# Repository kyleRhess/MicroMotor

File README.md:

# MicroMotor

## A three-phase BLDC motor driver with a rotary encoder interface and serial communication via USB.
## [More project details can be found here.](https://kylerhess.github.io/umotor.html)
\
 This code has been written for and tested on an ARM STM32F410 processor.
\
\
The rotary encoder interface was originally developed in my [EncoderQ](https://github.com/kyleRhess/EncoderQ) project.
\
\
The only rotary encoder that has been tested so far is the [Omron E6D-C](http://www.ia.omron.com/data_pdf/cat/e6d-c_ds_e_5_1_csm497.pdf).
\
\
The only BLDC motor that has been tested so far is the [Maxon EC 339268](https://www.maxongroup.com/medias/sys_master/root/8841185394718/EN-282.pdf). The motor requirement is that it must include Hall sensor output for position sensing. Back-EMF control is not currently supported.

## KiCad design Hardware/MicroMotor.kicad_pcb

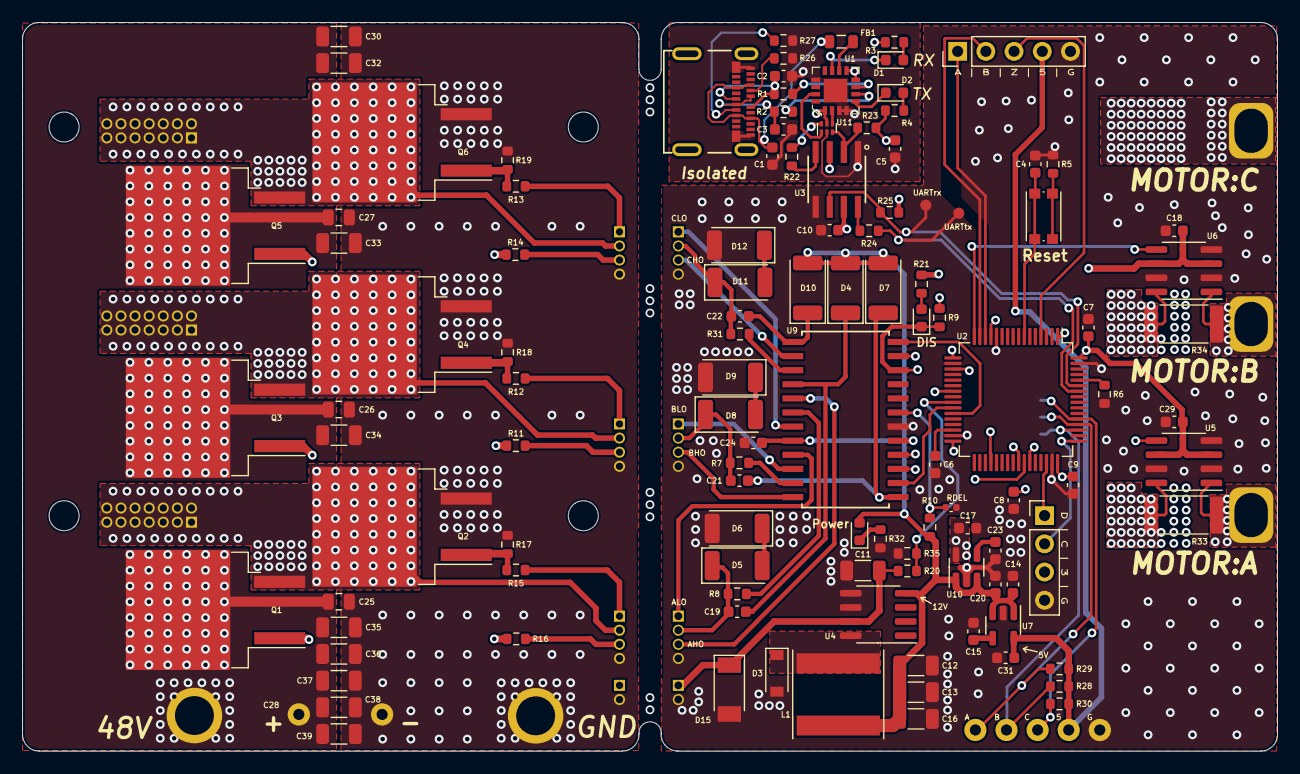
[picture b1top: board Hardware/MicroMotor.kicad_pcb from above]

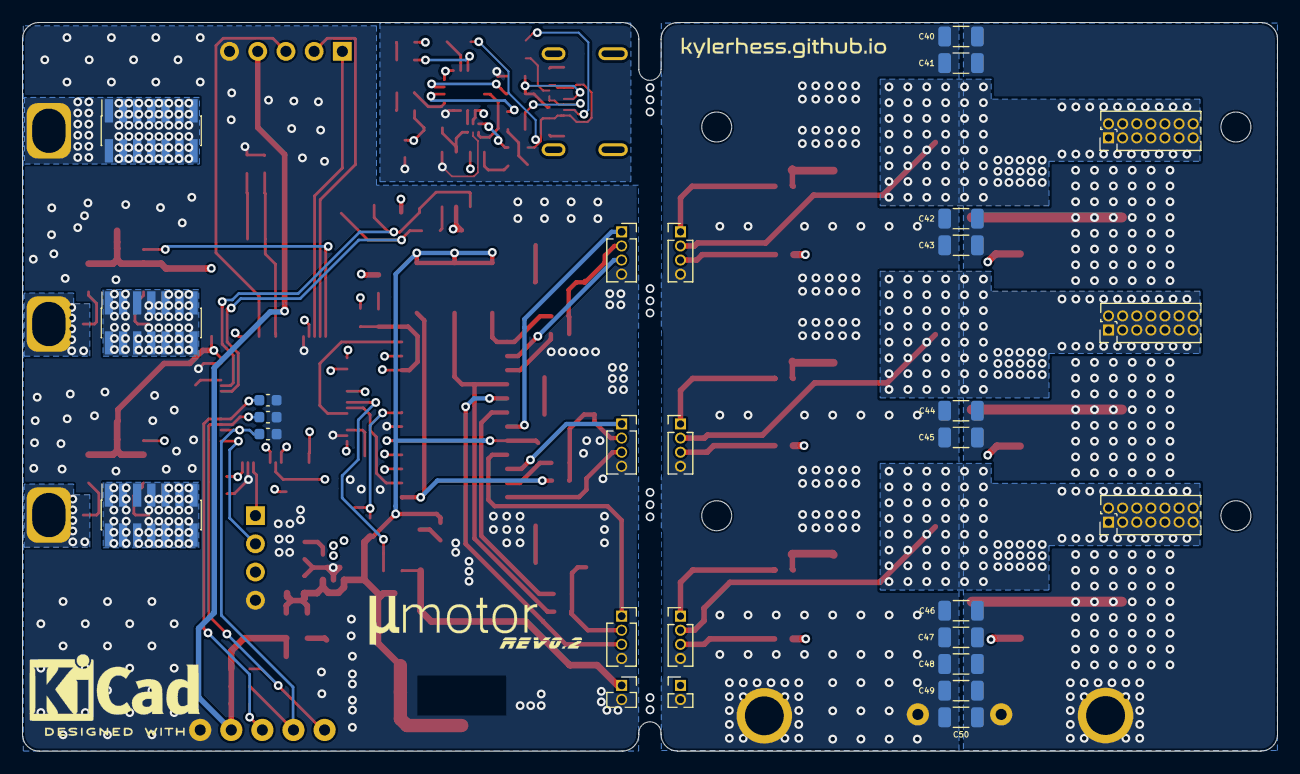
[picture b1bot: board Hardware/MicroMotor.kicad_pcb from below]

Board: 4 copper layers, 113.0 x 65.6 mm, 149 parts (28 on the bottom side), 81 nets.

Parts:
5: TestPoint_Loop_D2.50mm_Drill1.0mm
48V: TestPoint_THTPad_D4.0mm_Drill2.0mm
A: TestPoint_Plated_Hole_D3.0mm
A#2: TestPoint_Loop_D2.50mm_Drill1.0mm
B: TestPoint_Plated_Hole_D3.0mm
B#2: TestPoint_Loop_D2.50mm_Drill1.0mm
C: TestPoint_Plated_Hole_D3.0mm
C1, C9, C15, C23: 10nF; C_0603_1608Metric
C2, C3: 47pF; C_0603_1608Metric
C4, C5, C8, C10, C18, C29: 0.1uF; C_0603_1608Metric
C6, C7: 2.2uF; C_0603_1608Metric
C11: 1uF; C_1206_3216Metric
C12, C13, C16: 47uF; C_1206_3216Metric
C14, C17, C20, C24, C31: 1uF; C_0603_1608Metric
C19, C21, C22: 0.22uF; C_0603_1608Metric
C25, C26, C27: 1uF; C_0805_2012Metric
C28: 1000uF; C_Radial_D18.0mm_H35.5mm_P7.50mm
C30, C32, C33, C34, C35, C36, C37, C38, C39, C40, C41, C42, C43, C44, C45, C46, C47, C48, C49, C50: 4.7uF; C_1206_3216Metric
C#2: TestPoint_Loop_D2.50mm_Drill1.0mm
D1, D2, D13, D14: LED; LED_0603_1608Metric
D3: 60V 500mA; D_SOD-123
D4, D5, D6, D7, D8, D9, D10, D11, D12: D; D_2010_5025Metric
D15: SMA6S56A; D_SOD-128
FB1: 1.5A; L_0805_2012Metric
G: TestPoint_Loop_D2.50mm_Drill1.0mm
GND: TestPoint_THTPad_D4.0mm_Drill2.0mm
J1: USB_C_Receptacle_USB2.0; USB_C_1054500101
J2: Conn_01x04_Male; PinHeader_1x04_P2.54mm_Vertical
J3: Conn_01x05_Male; PinHeader_1x05_P2.54mm_Vertical
J4, J5, J6: Conn_01x04_Male; PinHeader_1x04_P1.27mm_Vertical
J7, J8, J9: Conn_02x06_Odd_Even; PinHeader_2x07_P1.27mm_Vertical
J10, J11, J12: Conn_02x06_Odd_Even; PinSocket_2x07_P1.27mm_Vertical_SMD
J13, J14, J15: Conn_01x04_Female; PinSocket_1x04_P1.27mm_Vertical
J16: Conn_01x02_Male; PinHeader_1x02_P1.27mm_Vertical
J17: Conn_01x02_Female; PinSocket_1x02_P1.27mm_Vertical
L1: 100uH; L_Taiyo-Yuden_NR-80xx
Q1, Q2, Q3, Q4, Q5, Q6: FDB075N15A; TO-263-2
R1, R2: 27; R_0603_1608Metric
R3, R4, R21, R22, R24: 330; R_0603_1608Metric
R5: 470; R_0603_1608Metric
R6, R20, R28, R29, R30, R32: 10k; R_0603_1608Metric
R7, R8, R31: 1.2; R_0603_1608Metric
R9, R17, R18, R19: 100k; R_0603_1608Metric
R10: 50k; R_0603_1608Metric
R11, R12, R13, R14, R15, R16: 22; R_0603_1608Metric
R23, R25: 1k; R_0603_1608Metric
R26, R27: 5.1k; R_0603_1608Metric
R33, R34: 750u; R_2512_6332Metric
R35: 576; R_0603_1608Metric
RDEL: C_0402_1005Metric
SW1: SW_Push; SW_Push_1P1T_NO_CK_KMR2
U1: FT230XQ-T; WQFN-16-1EP_4x4mm
U2: STM32F410RBTx; LQFP-64_10x10mm_P0.5mm
U3: ACSL-6210-00RE
U4: LM2594HVM-12; SOIC-8_3.9x4.9mm_P1.27mm
U5, U6: INA240A3D; SOIC-8_3.9x4.9mm_P1.27mm
U7: LP2985-5.0; SOT-23-5
U9: HIP4086ABZ
U10: LP2985-3.3; SOT-23-5
U11: NC7WZ04; Fairchild_MicroPak-6_1.0x1.45mm_P0.5mm
UARTrx: TestPoint_Pad_D1.0mm
UARTtx: TestPoint_Pad_D1.0mm

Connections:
3v3Out: C5.1, R3.1, R4.1, R23.1, U1.1, U1.8, U1.9, U3.3, U11.5
5V_Out: 5.1, C31.2, J3.4, R28.2, R29.2, R30.2, U7.5
12V_Out: C12.2, C13.2, C14.2, C16.2, C20.2, C24.1, D4.2, D7.2, D10.2, D13.2, L1.2, R10.1, U4.4, U7.1, U7.3, U9.20, U10.1, U10.3
+3V3: C7.1, C8.1, C9.1, C10.1, C17.2, C18.2, C29.2, J2.3, R9.1, R21.1, R25.1, U2.1, U2.13, U2.19, U2.32, U2.48, U2.64, U3.7, U5.3, U5.6, U6.3, U6.6, U10.5
+48V: 48V.1, C11.2, C25.1, C26.1, C27.1, C28.1, C30.1, C32.1, C33.1, C34.1, C35.1, C36.1, C37.1, C38.1, C39.1, C40.1, C41.1, C42.1, C43.1, C44.1, C45.1, C46.1, C47.1, C48.1, C49.1, C50.1, D15.1, J16.1, J17.1, Q1.2, Q3.2, Q5.2, R20.2, U4.7
-RXD: U1.2, U11.4
/VBUS: C1.1, FB1.2, J1.A4, J1.A9, J1.B4, J1.B9
AHB: C19.1, D4.1, U9.16
AHI: U2.23, U9.5
AHO: Q1.1, R16.2
AHO_r: J6.3, J15.3, R16.1, U9.17
ALI: U2.41, U9.4
ALO: Q2.1, R15.2, R17.1
ALO_r: J6.1, J15.1, R15.1, U9.21
A_OUT: A.1, R33.1, U5.1
A_SENS: U2.17, U5.5
BHB: C21.1, D7.1, U9.1
BHI: U2.26, U9.2
BHO: Q3.1, R11.2
BHO_r: J5.3, J14.3, R11.1, U9.24
BLI: U2.42, U9.3
BLO: Q4.1, R12.2, R18.1
BLO_r: J5.1, J14.1, R12.1, U9.22
B_OUT: B.1, R34.1, U6.1
B_SENS: U2.16, U6.5
CHB: C22.1, D10.1, U9.13
CHI: U2.27, U9.12
CHO: Q5.1, R14.2
CHO_r: J4.3, J13.3, R14.1, U9.14
CLI: U2.43, U9.11
CLO: Q6.1, R13.2, R19.1
CLO_r: J4.1, J13.1, R13.1, U9.19
DIS: D14.1, R9.2, U2.36, U9.10
Encod_A: J3.1, U2.14
Encod_B: J3.2, U2.15
Encod_Z: J3.3, U2.4
GND: C4.2, C6.2, C7.2, C8.2, C9.2, C10.2, C11.1, C12.1, C13.1, C14.1, C15.1, C16.1, C17.1, C18.1, C20.1, C23.1, C24.2, C25.2, C26.2, C27.2, C28.2, C29.1, C30.2, C31.1, C32.2, C33.2, C34.2, C35.2, C36.2, C37.2, C38.2, C39.2, C40.2, C41.2, C42.2, C43.2, C44.2, C45.2, C46.2, C47.2, C48.2, C49.2, C50.2, D3.2, D6.2, D9.2, D12.2, D15.2, G.1, GND.1, J2.4, J3.5, J4.4, J5.4, J6.4, J13.4, J14.4, J15.4, J16.2, J17.2, Q2.3, Q4.3, Q6.3, R5.1, R6.1, R17.2, R18.2, R19.2, R32.1, R35.1, RDEL.2, U2.12, U2.18, U2.31, U2.47, U2.63, U3.5, U4.5, U4.6, U5.2, U5.4, U5.7, U6.2, U6.4, U6.7, U7.2, U9.6, U10.2
GNDS: C1.2, C2.2, C3.2, C5.2, J1.A1, J1.A12, J1.B1, J1.B12, R26.2, R27.2, U1.3, U1.4, U1.13, U1.17, U3.1, U11.2
HALL_A: A#2.1, R29.1, U2.52
HALL_B: B#2.1, R28.1, U2.51
HALL_C: C#2.1, R30.1, U2.53
MTR_A: C19.2, D5.1, J6.2, J9.1, J9.2, J9.3, J9.4, J9.5, J9.6, J9.7, J9.8, J9.9, J9.10, J9.11, J9.12, J9.13, J9.14, J12.1, J12.2, J12.3, J12.4, J12.5, J12.6, J12.7, J12.8, J12.9, J12.10, J12.11, J12.12, J12.13, J12.14, J15.2, Q1.3, Q2.2, R8.2, R33.2, U5.8
MTR_B: C21.2, D8.1, J5.2, J8.1, J8.2, J8.3, J8.4, J8.5, J8.6, J8.7, J8.8, J8.9, J8.10, J8.11, J8.12, J8.13, J8.14, J11.1, J11.2, J11.3, J11.4, J11.5, J11.6, J11.7, J11.8, J11.9, J11.10, J11.11, J11.12, J11.13, J11.14, J14.2, Q3.3, Q4.2, R7.2, R34.2, U6.8
MTR_C: C.1, C22.2, D11.1, J4.2, J7.1, J7.2, J7.3, J7.4, J7.5, J7.6, J7.7, J7.8, J7.9, J7.10, J7.11, J7.12, J7.13, J7.14, J10.1, J10.2, J10.3, J10.4, J10.5, J10.6, J10.7, J10.8, J10.9, J10.10, J10.11, J10.12, J10.13, J10.14, J13.2, Q5.3, Q6.2, R31.2
unnamed: C2.1, J1.A7, J1.B7, R1.1
unnamed: C3.1, J1.A6, J1.B6, R2.2
unnamed: C4.1, SW1.2, U2.7
unnamed: C6.1, U2.30
unnamed: C15.2, U7.4
unnamed: C23.2, U10.4
unnamed: D1.1, U1.11
unnamed: D1.2, R3.2
unnamed: D2.1, U1.5
unnamed: D2.2, R4.2
unnamed: D3.1, L1.1, U4.8
unnamed: D5.2, D6.1
unnamed: D8.2, D9.1
unnamed: D11.2, D12.1
unnamed: D13.1, R32.2
unnamed: D14.2, R21.2
unnamed: FB1.1, U1.10
unnamed: J1.A5, R26.1
unnamed: J1.B5, R27.1
unnamed: R1.2, U1.7
unnamed: R2.1, U1.6
unnamed: R5.2, SW1.1
unnamed: R6.2, U2.60
unnamed: R7.1, U9.23
unnamed: R8.1, U9.18
unnamed: R22.1, U3.4
unnamed: R22.2, U11.6
unnamed: R24.1, U3.8
unnamed: R31.1, U9.15
unnamed: U1.15, U11.1
RDEL: R10.2, RDEL.1, U9.7
RXD: R23.2, U3.2, U11.3
SWCLK: J2.2, U2.49
SWDIO: J2.1, U2.46
USART1_RX: R25.2, U2.59, U3.6, UARTrx.1
USART1_TX: R24.2, U2.58, UARTtx.1
VBAT_MEAS: R20.1, R35.2, U2.25

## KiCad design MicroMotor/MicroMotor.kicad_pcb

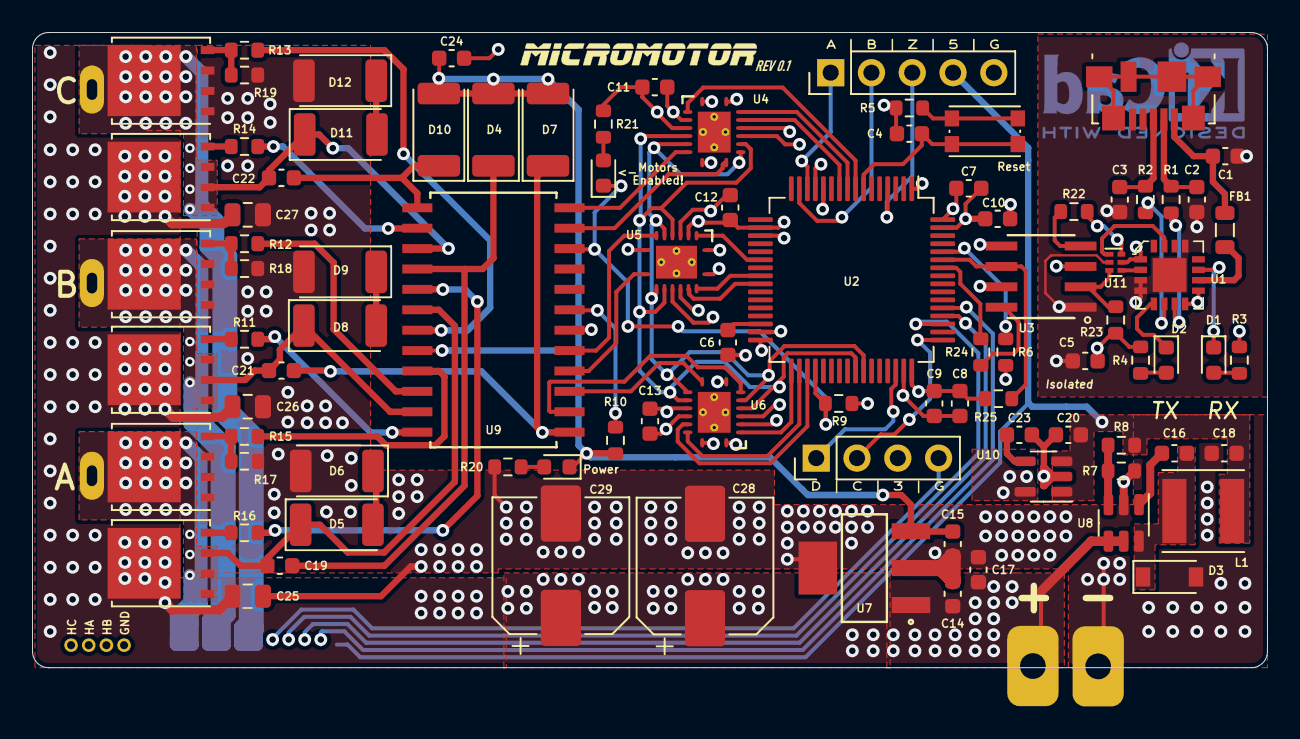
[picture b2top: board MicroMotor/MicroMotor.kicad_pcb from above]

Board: 4 copper layers, 76.9 x 39.5 mm, 97 parts (1 on the bottom side), 83 nets.

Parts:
C1, C9, C23: 10nF; C_0603_1608Metric
C2, C3: 47pF; C_0603_1608Metric
C4, C5, C8, C10, C11, C12, C13: 0.1uF; C_0603_1608Metric
C6, C7, C17: 2.2uF; C_0603_1608Metric
C14: 0.47uF; C_0603_1608Metric
C15: 22uF; C_0603_1608Metric
C16: 0.15uF; C_0603_1608Metric
C18: 47uF; C_0603_1608Metric
C19, C21, C22: 0.22uF; C_0603_1608Metric
C20, C24: 1uF; C_0603_1608Metric
C25, C26, C27: 1uF; C_0805_2012Metric
C28, C29: 220uF 50V; CP_Elec_8x10
D1, D2, D13, D14: LED; LED_0603_1608Metric
D3: 60V 500mA; D_SOD-123
D4, D5, D6, D7, D8, D9, D10, D11, D12: D; D_2010_5025Metric
FB1: 1.5A; L_0805_2012Metric
J1: USB_B_Micro; USB_Micro-B_Molex_47346-0001
J2: Conn_01x04_Male; PinHeader_1x04_P2.54mm_Vertical
J3: Conn_01x05_Male; PinHeader_1x05_P2.54mm_Vertical
J4: Conn_01x02_Female; PinHeader_1x2_P2.54mm
J5: Conn_01x11_Female; Molex_200528-0110_1x11-1MP_P1.00mm_Horizontal
J8, J8#2, J8#3, J8#4: Conn_01x01_Male; Pin_D0.5mm_L6.5mm_W1.8mm_FlatFork
L1: 15uH; L_Taiyo-Yuden_NR-50xx
Q1, Q2, Q3, Q4, Q5, Q6: CSD18537NQ5A; TDSON-8-1
R1, R2: 27; R_0603_1608Metric
R3, R4, R21, R22, R24: 330; R_0603_1608Metric
R5: 470; R_0603_1608Metric
R6, R20: 10k; R_0603_1608Metric
R7: 1.02k; R_0603_1608Metric
R8: 5.62k; R_0603_1608Metric
R9, R17, R18, R19: 100k; R_0603_1608Metric
R10: 50k; R_0603_1608Metric
R11, R12, R13, R14, R15, R16: 22; R_0603_1608Metric
R23, R25: 1k; R_0603_1608Metric
SW1: SW_Push; SW_Push_1P1T_NO_CK_KMR2
U1: FT230XQ-T; WQFN-16-1EP_4x4mm
U2: STM32F410RBTx; LQFP-64_10x10mm_P0.5mm
U3: ACSL-6210-00RE
U4, U5, U6: SN74CB3Q3253RGYR
U7: LM2940IMP-10_NOPB; LM2940IMP-10
U8: LMR14203; TSOT-23-6
U9: HIP4086ABZ
U10: LP2985-3.3; SOT-23-5
U11: NC7WZ04; Fairchild_MicroPak-6_1.0x1.45mm_P0.5mm

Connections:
3v3Out: C5.1, R3.1, R4.1, R23.1, U1.1, U1.8, U1.9, U3.3, U11.5
5V_Out: C18.2, C20.2, J3.4, J5.11, L1.2, R8.2, U10.1, U10.3
+3V3: C7.1, C8.1, C9.1, C10.1, C11.2, C12.2, C13.2, J2.3, R9.1, R21.1, R25.1, U2.1, U2.13, U2.19, U2.32, U2.48, U2.64, U3.7, U4.4, U4.12, U4.16, U5.4, U5.12, U5.16, U6.4, U6.12, U6.16, U10.5
+10V: C15.2, C24.1, D4.2, D7.2, D10.2, D13.1, R10.1, U7.3, U9.20
+PWM: U2.42, U4.6, U4.10, U5.6, U5.10, U6.6, U6.10
+VDC: C14.2, C17.1, C25.1, C26.1, C27.1, C28.1, C29.1, J4.1, Q1.5, Q3.5, Q5.5, U7.1, U8.4, U8.5
-PWM: U2.41, U4.5, U4.11, U5.5, U5.11, U6.5, U6.11
-RXD: U1.2, U11.4
AHB: C19.1, D4.1, U9.16
AHI: U5.7, U9.5
AHO: Q1.4, R16.2
ALI: U5.9, U9.4
ALO: Q2.4, R15.2, R17.1
AL_EN: U2.9, U4.15
BHB: C21.1, D7.1, U9.1
BHI: U6.7, U9.2
BHO: Q3.4, R11.2
BLI: U6.9, U9.3
BLO: Q4.4, R12.2, R18.1
BL_EN: U2.24, U5.15
CHB: C22.1, D10.1, U9.13
CHI: U4.7, U9.12
CHO: Q5.4, R14.2
CLI: U4.9, U9.11
CLO: Q6.4, R13.2, R19.1
CL_EN: U2.34, U6.15
DIS: D14.1, R9.2, U2.36, U9.10
Encod_A: J3.1, U2.14
Encod_B: J3.2, U2.15
Encod_Z: J3.3, U2.4
GND: C4.2, C6.2, C7.2, C8.2, C9.2, C10.2, C11.1, C12.1, C13.1, C14.1, C15.1, C17.2, C18.1, C20.1, C23.1, C24.2, C25.2, C26.2, C27.2, C28.2, C29.2, D3.2, D6.2, D9.2, D12.2, J2.4, J3.5, J4.2, J5.7, J8.1, Q2.1, Q2.2, Q2.3, Q4.1, Q4.2, Q4.3, Q6.1, Q6.2, Q6.3, R5.1, R6.1, R7.1, R17.2, R18.2, R19.2, R20.1, U2.12, U2.18, U2.31, U2.47, U2.63, U3.5, U4.1, U4.3, U4.8, U4.13, U5.1, U5.3, U5.8, U5.13, U6.1, U6.3, U6.8, U6.13, U7.2, U7.4, U8.2, U9.6, U10.2
GNDS: C1.2, C2.2, C3.2, C5.2, J1.5, U1.3, U1.4, U1.13, U1.17, U3.1, U11.2
HALL_A: J5.9, J8#3.1, U2.52
HALL_B: J5.8, J8#2.1, U2.51
HALL_C: J5.10, J8#4.1, U2.53
MTR_A: C19.2, D5.1, J5.1, J5.2, Q1.1, Q1.2, Q1.3, Q2.5, U9.18
MTR_B: C21.2, D8.1, J5.3, J5.4, Q3.1, Q3.2, Q3.3, Q4.5, U9.23
MTR_C: C22.2, D11.1, J5.5, J5.6, Q5.1, Q5.2, Q5.3, Q6.5, U9.15
unnamed: C1.1, FB1.2, J1.1
unnamed: C2.1, J1.2, R1.1
unnamed: C3.1, J1.3, R2.2
unnamed: C4.1, SW1.2, U2.7
unnamed: C6.1, U2.30
unnamed: C16.1, D3.1, L1.1, U8.6
unnamed: C16.2, U8.1
unnamed: C23.2, U10.4
unnamed: D1.1, U1.11
unnamed: D1.2, R3.2
unnamed: D2.1, U1.5
unnamed: D2.2, R4.2
unnamed: D5.2, D6.1
unnamed: D8.2, D9.1
unnamed: D11.2, D12.1
unnamed: D13.2, R20.2
unnamed: D14.2, R21.2
unnamed: FB1.1, U1.10
unnamed: R1.2, U1.7
unnamed: R2.1, U1.6
unnamed: R5.2, SW1.1
unnamed: R6.2, U2.60
unnamed: R7.2, R8.1, U8.3
unnamed: R10.2, U9.7
unnamed: R11.1, U9.24
unnamed: R12.1, U9.22
unnamed: R13.1, U9.19
unnamed: R14.1, U9.14
unnamed: R15.1, U9.21
unnamed: R16.1, U9.17
unnamed: R22.1, U3.4
unnamed: R22.2, U11.6
unnamed: R24.1, U3.8
unnamed: U1.15, U11.1
RXD: R23.2, U3.2, U11.3
SWCLK: J2.2, U2.49
SWDIO: J2.1, U2.46
S_0: U2.10, U4.14
S_1: U2.8, U4.2
S_2: U2.25, U5.14
S_3: U2.22, U5.2
S_4: U2.35, U6.14
S_5: U2.33, U6.2
USART1_RX: R25.2, U2.59, U3.6
USART1_TX: R24.2, U2.58

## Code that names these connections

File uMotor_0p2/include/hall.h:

#ifndef HALL_H_ /* include guard */
#define HALL_H_

#include "system.h"

// Hall sensor states
#define HALL_A			0
#define HALL_B			1
#define HALL_C			2

//GPIOC
#define GPIO_S0_PIN		GPIO_PIN_2
#define GPIO_S1_PIN		GPIO_PIN_0
#define GPIO_S2_PIN		GPIO_PIN_5
#define GPIO_ALEN_PIN	GPIO_PIN_1
#define GPIO_BLEN_PIN	GPIO_PIN_4

//GPIOA
#define GPIO_S3_PIN		GPIO_PIN_6

//GPIOB
#define GPIO_S4_PIN		GPIO_PIN_14
#define GPIO_S5_PIN		GPIO_PIN_12
#define GPIO_CLEN_PIN	GPIO_PIN_13
#define GPIO_DIS_PIN	GPIO_PIN_15

//MUX States
#define MUX_A				0x0A
#define MUX_B				0x0B
#define MUX_C				0x0C
#define	MUX_STATE_P_PWM		0x01
#define	MUX_STATE_M_PWM		0x02
#define	MUX_STATE_HI		0x03
#define	MUX_STATE_Z			0x04
#define	MUX_STATE_LO		0x05
#define	MUX_STATE_P_PWM_T	0x06
#define	MUX_STATE_M_PWM_T	0x07
#define	MUX_STATE_TBD4		0x08

// Read a GPIO state (returns GPIO_PIN_X)
#define READ_H(xxx)	(HALL_PORT->IDR & xxx)

// Test for 1/6 states
#define STATE_1		READ_H(HALL_A_PIN) 	&& !READ_H(HALL_B_PIN) 	&& !READ_H(HALL_C_PIN)
#define STATE_2		READ_H(HALL_A_PIN) 	&& READ_H(HALL_B_PIN) 	&& !READ_H(HALL_C_PIN)
#define STATE_3		!READ_H(HALL_A_PIN) && READ_H(HALL_B_PIN) 	&& !READ_H(HALL_C_PIN)
#define STATE_4		!READ_H(HALL_A_PIN) && READ_H(HALL_B_PIN) 	&& READ_H(HALL_C_PIN)
#define STATE_5		!READ_H(HALL_A_PIN) && !READ_H(HALL_B_PIN) 	&& READ_H(HALL_C_PIN)
#define STATE_6		READ_H(HALL_A_PIN) 	&& !READ_H(HALL_B_PIN) 	&& READ_H(HALL_C_PIN)


void Hall_ComputeRPM(float timeStep);
void Hall_InputInit(void);
float Hall_GetRPM(void);
uint32_t Hall_GetSteps(void);
void Hall_SetSteps(uint32_t val);


#endif /* HALL_H_ */

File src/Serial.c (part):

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		}
		else
		{
			WritePin(GPIOB, GPIO_DIS_PIN, !ReadPin(GPIOB, GPIO_DIS_PIN));
		}
	}

//	switch (command)
//	{
//		case 0xabcd:
//			WritePin(GPIOB, GPIO_DIS_PIN, !ReadPin(GPIOB, GPIO_DIS_PIN));
//			break;
//		default:
//			break;
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
	    __HAL_RCC_GPIOB_CLK_ENABLE();
	    /**USART1 GPIO Configuration
	    PB6     ------> USART1_TX
	    PB7     ------> USART1_RX
	    */
	    GPIO_InitStruct.Pin 					= UART_TX_PIN | UART_RX_PIN;
	    GPIO_InitStruct.Mode 					= GPIO_MODE_AF_PP;
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    __HAL_RCC_USART1_CLK_DISABLE();

    /**USART1 GPIO Configuration
    PB6     ------> USART1_TX
    PB7     ------> USART1_RX
    */
    HAL_GPIO_DeInit(UART_PORT, UART_TX_PIN | UART_RX_PIN);

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
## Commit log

2020-11-06 Totally changed MOSFET layout. Added PWR and enabled LEDs
2020-11-07 Exposed hall nets for external use
2020-11-09 Added inverter logic to USB side since isolator inverts signals. Added pull-ups on optoisolator. Fix some silkscreens.
2020-11-09 Ordered boards
2020-11-12 Initial firmware project made. Moved PCB files to Hardware directory.
2020-12-03 Initial working firmware with hall ISR noise filtering.
2020-12-12 Refactored and added messaging for PC interface.
2020-12-14 More refactoring. Fixed fatal bug from previous refactoring. Working now.
2020-12-26 Minor refactor of pwm.c
2021-01-16 Began mux remove and part consolidation
2021-01-22 Began making changes for 48V version.
2021-01-27 Nearly finished board and schematic changes for FOC and high current.
2021-02-02 Made board into pluggable two-board solution.
2021-02-03 More board finalization. More low ESR caps on power stage. Silkscreen fixes.
2021-02-09 More board refinements
2021-02-11 Changed board connectors to 1.27mm pitch. Nearly done.
2021-02-11 Minor update to BOM
2021-02-11 Added UART pads
2021-02-11 Deleted extra pad
2021-03-08 Wiped out old firmware and replaced with new FOC project. Initial FOC algo working.
2021-03-11 Tuned torque/speed/position controllers. Working well... mostly...
2021-03-13 Moved FOC calc call to end of ADC complete ISR.
2021-03-15 Tuned speed and position loops more. Working a little better now.
2021-03-16 Started code refactor and clean-up.
2021-03-17 Further code cleanup. Added homing feature. Started refactoring state monitor.
2021-03-20 Continued refactor. Noticed issue with rotor angle values growing too large. Floating point losing precision.
2021-03-23 Minor clean up. Fixed potential clock overflow bug.
2021-03-24 Minor refactoring. Switched PI controllers to use double precision floats. Same for rotor angle. This partially mitigates the issue with growing encoder values.
2021-03-26 Further testing and optimization of PWM frequency to ensure timing is accurate.
2021-03-27 Fixed bug with speed calc that occurs when clock timer rolls over.
2021-04-18 Working version still in test.
2021-05-09 Initial version for ebike. Still testing.
2021-05-10 More updates for ebike. Modified serial interface to work with external HID.
2021-05-23 Stopped receiving of UART bytes. Added support for throttle input. First test with bike, but wheel came off.
2021-06-20 Added missing timer init.
2021-07-13 Schematic PN update.
2021-07-13 Updated current sense IC to 20V/V part.
2021-07-13 Added tantalum cap to 12V reg.
2021-07-13 Changed 5V linear reg to switching type.
2021-07-13 Added filter caps to Hall sensor inputs.
2022-03-12 Stuff for C project

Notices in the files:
parts and their libraries:
Copyright 2016 Accelerated Designs. All rights reserved.
